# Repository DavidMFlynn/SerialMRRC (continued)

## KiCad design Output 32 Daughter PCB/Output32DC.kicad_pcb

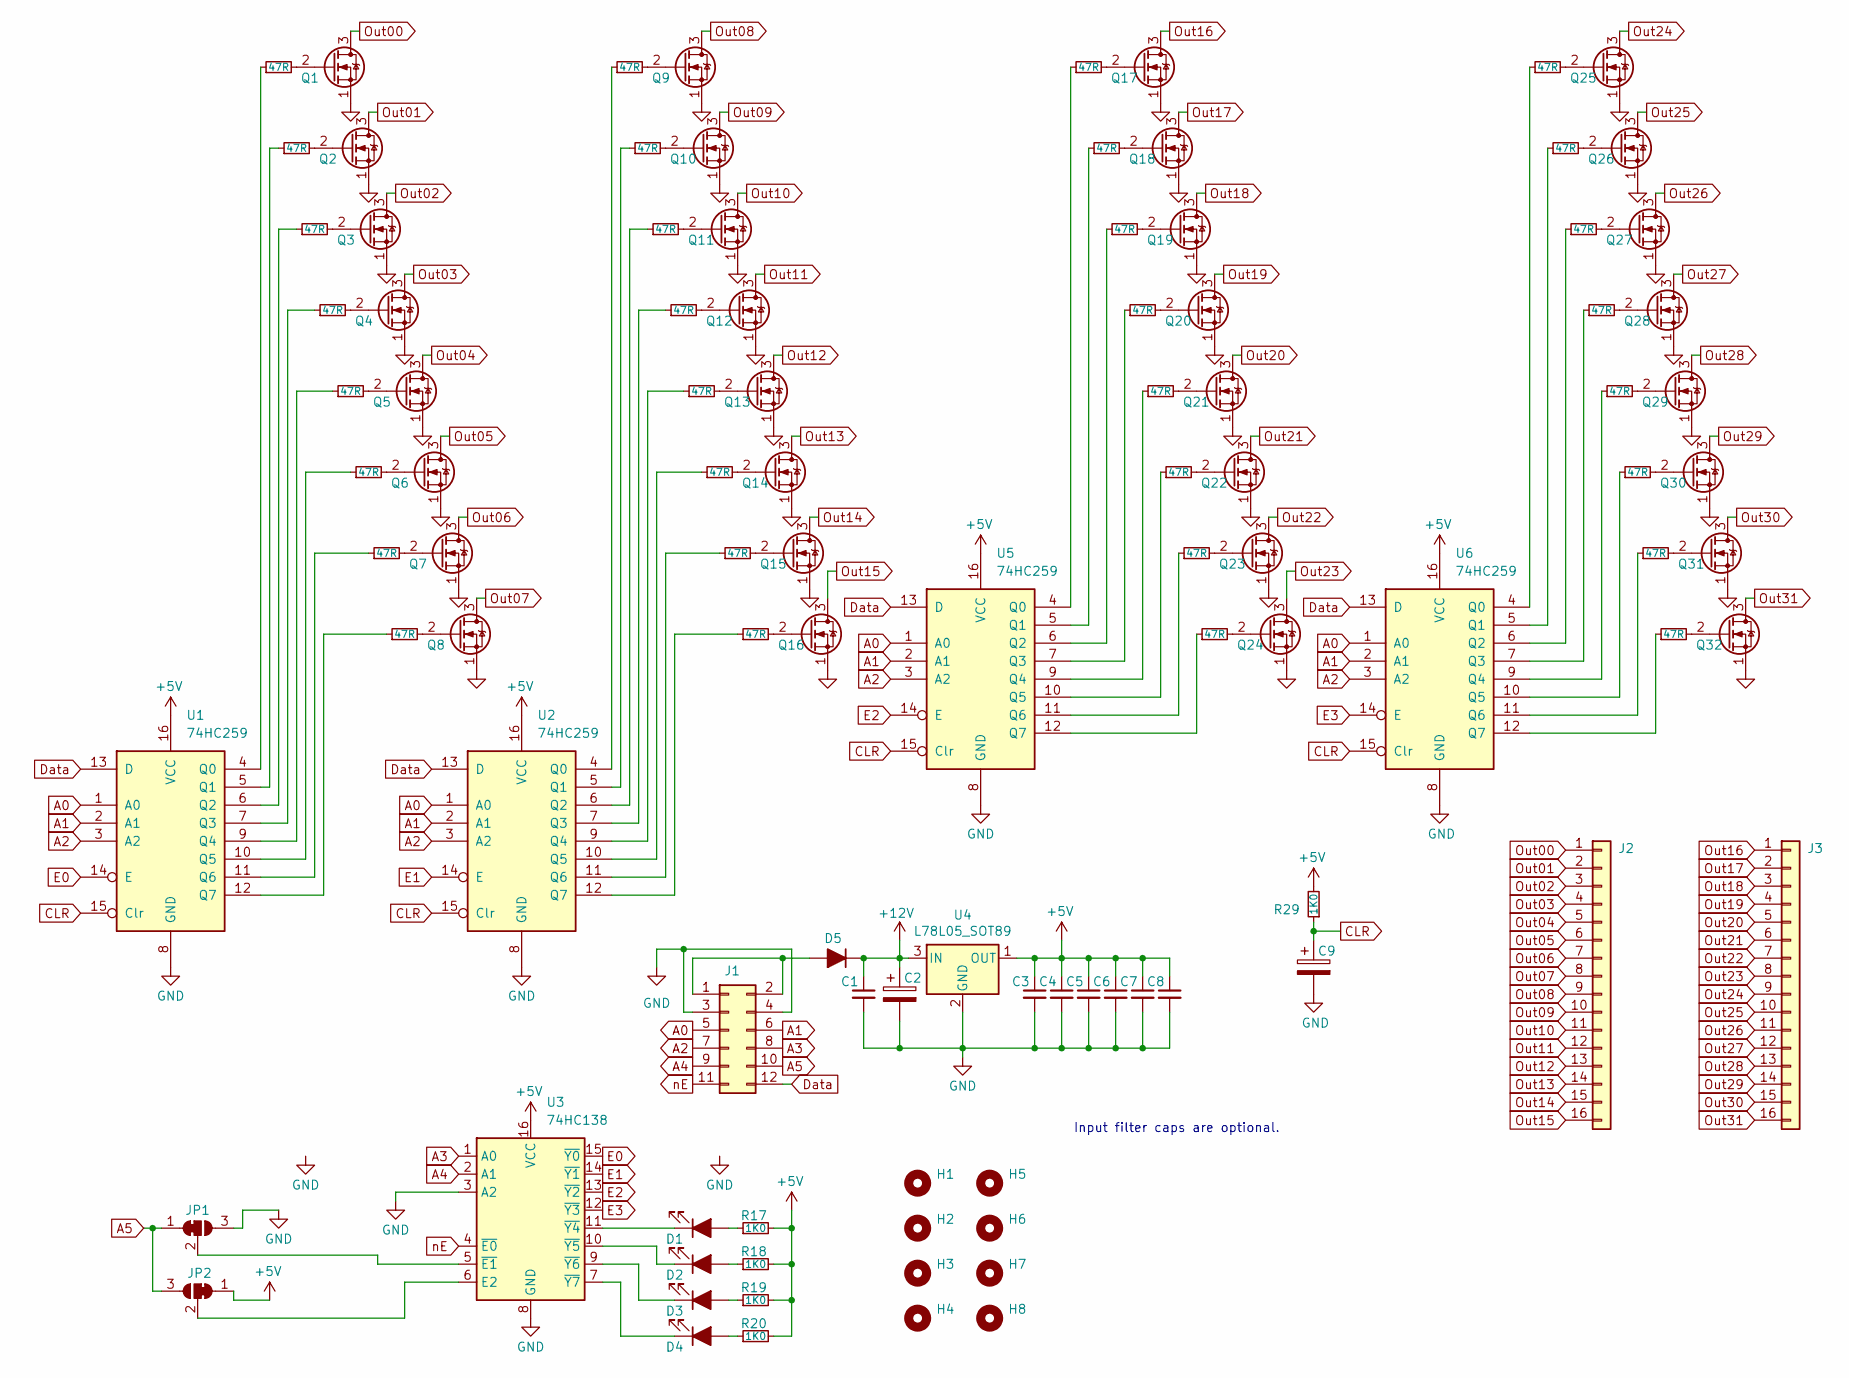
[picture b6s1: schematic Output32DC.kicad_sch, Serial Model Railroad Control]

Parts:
C1, C3, C4, C5, C6, C7, C8: 0.1uF; C_0805_2012Metric_Pad1.18x1.45mm_HandSolder
C2, C9: 10uF; CP_Radial_D5.0mm_P2.00mm
D1, D2, D3, D4: 1206 LED; LED_1206_3216Metric_Pad1.42x1.75mm_HandSolder
D5: SMA; D_SMA_Handsoldering
H1, H2, H3, H4: MountingHole; MountingHole_4.3mm_M4
H5, H6, H7, H8: MountingHole; MountingHole_3.2mm_M3
J1: Conn_02x06_Odd_Even; PinHeader_2x06_P2.54mm_Vertical
J2, J3: Conn_01x16; TerminalBlock_Phoenix_PT-1,5-16-3.5-H_1x16_P3.50mm_Horizont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
JP1, JP2: SolderJumper_3_Bridged12; SolderJumper-3_P1.3mm_Bridged12_RoundedPad1.0x1.5mm
Q1, Q2, Q3, Q4, Q5, Q6, Q7, Q8, Q9, Q10, Q11, Q12, Q13, Q14, Q15, Q16, Q17, Q18, Q19, Q20, Q21, Q22, Q23, Q24, Q25, Q26, Q27, Q28, Q29, Q30, Q31, Q32: 2N7000; TO-92_Inline
R1, R2, R3, R4, R5, R6, R7, R8, R9, R10, R11, R12, R13, R14, R15, R16, R21, R22, R23, R24, R25, R26, R27, R28, R30, R31, R32, R33, R34, R35, R36, R37: 47R; R_0805_2012Metric_Pad1.20x1.40mm_HandSolder
R17, R18, R19, R20, R29: 1K0; R_0805_2012Metric_Pad1.20x1.40mm_HandSolder
U1, U2, U5, U6: 74HC259; SOIC-16_3.9x9.9mm_P1.27mm
U3: 74HC138; SOIC-16_3.9x9.9mm_P1.27mm
U4: L78L05_SOT89; SOT-89-3

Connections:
+5V: C3.1, C4.1, C5.1, C6.1, C7.1, C8.1, JP2.1 (A), R17.2, R18.2, R19.2, R20.2, R29.2, U1.16 (VCC), U2.16 (VCC), U3.16 (VCC), U4.1 (OUT), U5.16 (VCC), U6.16 (VCC)
+12V: C1.1, C2.1, D5.1 (K), U4.3 (IN)
A0: J1.5, U1.1 (A0), U2.1 (A0), U5.1 (A0), U6.1 (A0)
A1: J1.6, U1.2 (A1), U2.2 (A1), U5.2 (A1), U6.2 (A1)
A2: J1.7, U1.3 (A2), U2.3 (A2), U5.3 (A2), U6.3 (A2)
A3: J1.8, U3.1 (A0)
A4: J1.9, U3.2 (A1)
A5: J1.10, JP1.1 (A), JP2.3 (B)
CLR: C9.1, R29.1, U1.15 (Clr), U2.15 (Clr), U5.15 (Clr), U6.15 (Clr)
Data: J1.12, U1.13 (D), U2.13 (D), U5.13 (D), U6.13 (D)
E0: U1.14 (E), U3.15 (~Y0)
E1: U2.14 (E), U3.14 (~Y1)
E2: U3.13 (~Y2), U5.14 (E)
E3: U3.12 (~Y3), U6.14 (E)
GND: C1.2, C2.2, C3.2, C4.2, C5.2, C6.2, C7.2, C8.2, C9.2, J1.3, J1.4, JP1.3 (B), Q1.1 (S), Q2.1 (S), Q3.1 (S), Q4.1 (S), Q5.1 (S), Q6.1 (S), Q7.1 (S), Q8.1 (S), Q9.1 (S), Q10.1 (S), Q11.1 (S), Q12.1 (S), Q13.1 (S), Q14.1 (S), Q15.1 (S), Q16.1 (S), Q17.1 (S), Q18.1 (S), Q19.1 (S), Q20.1 (S), Q21.1 (S), Q22.1 (S), Q23.1 (S), Q24.1 (S), Q25.1 (S), Q26.1 (S), Q27.1 (S), Q28.1 (S), Q29.1 (S), Q30.1 (S), Q31.1 (S), Q32.1 (S), U1.8 (GND), U2.8 (GND), U3.3 (A2), U3.8 (GND), U4.2 (GND), U5.8 (GND), U6.8 (GND)
unnamed: D1.2 (A), R17.1
unnamed: D1.1 (K), U3.11 (~Y4)
unnamed: D2.2 (A), R18.1
unnamed: D2.1 (K), U3.10 (~Y5)
unnamed: D3.2 (A), R19.1
unnamed: D3.1 (K), U3.9 (~Y6)
unnamed: D4.2 (A), R20.1
unnamed: D4.1 (K), U3.7 (~Y7)
unnamed: D5.2 (A), J1.1, J1.2
unnamed: JP1.2 (C), U3.5 (~E1)
unnamed: JP2.2 (C), U3.6 (E2)
unnamed: Q1.2 (G), R1.2
unnamed: Q2.2 (G), R2.2
unnamed: Q3.2 (G), R3.2
unnamed: Q4.2 (G), R4.2
unnamed: Q5.2 (G), R5.2
unnamed: Q6.2 (G), R6.2
unnamed: Q7.2 (G), R7.2
unnamed: Q8.2 (G), R8.2
unnamed: Q9.2 (G), R9.2
unnamed: Q10.2 (G), R10.2
unnamed: Q11.2 (G), R11.2
unnamed: Q12.2 (G), R12.2
unnamed: Q13.2 (G), R13.2
unnamed: Q14.2 (G), R14.2
unnamed: Q15.2 (G), R15.2
unnamed: Q16.2 (G), R16.2
unnamed: Q17.2 (G), R21.2
unnamed: Q18.2 (G), R22.2
unnamed: Q19.2 (G), R23.2
unnamed: Q20.2 (G), R24.2
unnamed: Q21.2 (G), R25.2
unnamed: Q22.2 (G), R26.2
unnamed: Q23.2 (G), R27.2
unnamed: Q24.2 (G), R28.2
unnamed: Q25.2 (G), R30.2
unnamed: Q26.2 (G), R31.2
unnamed: Q27.2 (G), R32.2
unnamed: Q28.2 (G), R33.2
unnamed: Q29.2 (G), R34.2
unnamed: Q30.2 (G), R35.2
unnamed: Q31.2 (G), R36.2
unnamed: Q32.2 (G), R37.2
unnamed: R1.1, U1.4 (Q0)
unnamed: R2.1, U1.5 (Q1)
unnamed: R3.1, U1.6 (Q2)
unnamed: R4.1, U1.7 (Q3)
unnamed: R5.1, U1.9 (Q4)
unnamed: R6.1, U1.10 (Q5)
unnamed: R7.1, U1.11 (Q6)
unnamed: R8.1, U1.12 (Q7)
unnamed: R9.1, U2.4 (Q0)
unnamed: R10.1, U2.5 (Q1)
unnamed: R11.1, U2.6 (Q2)
unnamed: R12.1, U2.7 (Q3)
unnamed: R13.1, U2.9 (Q4)
unnamed: R14.1, U2.10 (Q5)
unnamed: R15.1, U2.11 (Q6)
unnamed: R16.1, U2.12 (Q7)
unnamed: R21.1, U5.4 (Q0)
unnamed: R22.1, U5.5 (Q1)
unnamed: R23.1, U5.6 (Q2)
unnamed: R24.1, U5.7 (Q3)
unnamed: R25.1, U5.9 (Q4)
unnamed: R26.1, U5.10 (Q5)
unnamed: R27.1, U5.11 (Q6)
unnamed: R28.1, U5.12 (Q7)
unnamed: R30.1, U6.4 (Q0)
unnamed: R31.1, U6.5 (Q1)
unnamed: R32.1, U6.6 (Q2)
unnamed: R33.1, U6.7 (Q3)
unnamed: R34.1, U6.9 (Q4)
unnamed: R35.1, U6.10 (Q5)
unnamed: R36.1, U6.11 (Q6)
unnamed: R37.1, U6.12 (Q7)
Out00: J2.1, Q1.3 (D)
Out01: J2.2, Q2.3 (D)
Out02: J2.3, Q3.3 (D)
Out03: J2.4, Q4.3 (D)
Out04: J2.5, Q5.3 (D)
Out05: J2.6, Q6.3 (D)
Out06: J2.7, Q7.3 (D)
Out07: J2.8, Q8.3 (D)
Out08: J2.9, Q9.3 (D)
Out09: J2.10, Q10.3 (D)
Out10: J2.11, Q11.3 (D)
Out11: J2.12, Q12.3 (D)
Out12: J2.13, Q13.3 (D)
Out13: J2.14, Q14.3 (D)
Out14: J2.15, Q15.3 (D)
Out15: J2.16, Q16.3 (D)
Out16: J3.1, Q17.3 (D)
Out17: J3.2, Q18.3 (D)
Out18: J3.3, Q19.3 (D)
Out19: J3.4, Q20.3 (D)
Out20: J3.5, Q21.3 (D)
Out21: J3.6, Q22.3 (D)
Out22: J3.7, Q23.3 (D)
Out23: J3.8, Q24.3 (D)
Out24: J3.9, Q25.3 (D)
Out25: J3.10, Q26.3 (D)
Out26: J3.11, Q27.3 (D)
Out27: J3.12, Q28.3 (D)
Out28: J3.13, Q29.3 (D)
Out29: J3.14, Q30.3 (D)
Out30: J3.15, Q31.3 (D)
Out31: J3.16, Q32.3 (D)
nE: J1.11, U3.4 (~E0)

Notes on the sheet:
Input filter caps are optional.

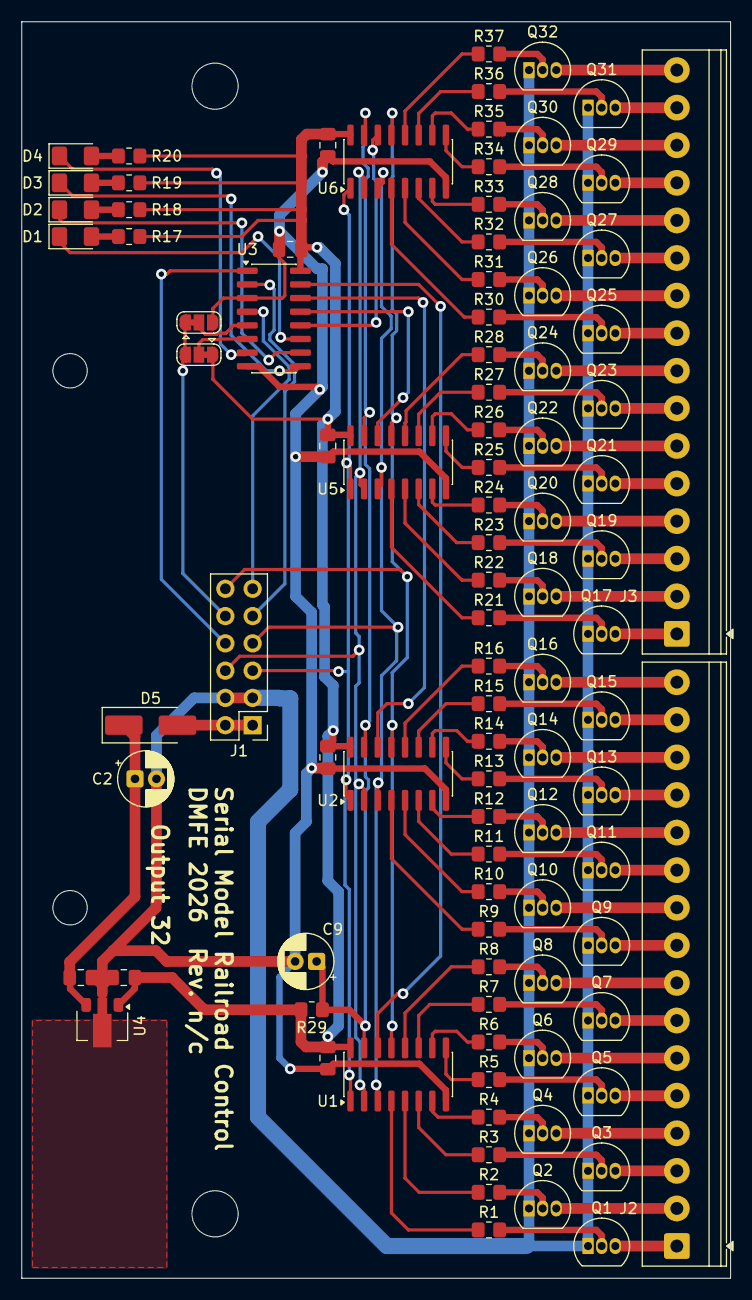
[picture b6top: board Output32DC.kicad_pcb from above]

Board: 2 copper layers, 66.0 x 117.0 mm, 98 parts (0 on the bottom side), 123 nets.

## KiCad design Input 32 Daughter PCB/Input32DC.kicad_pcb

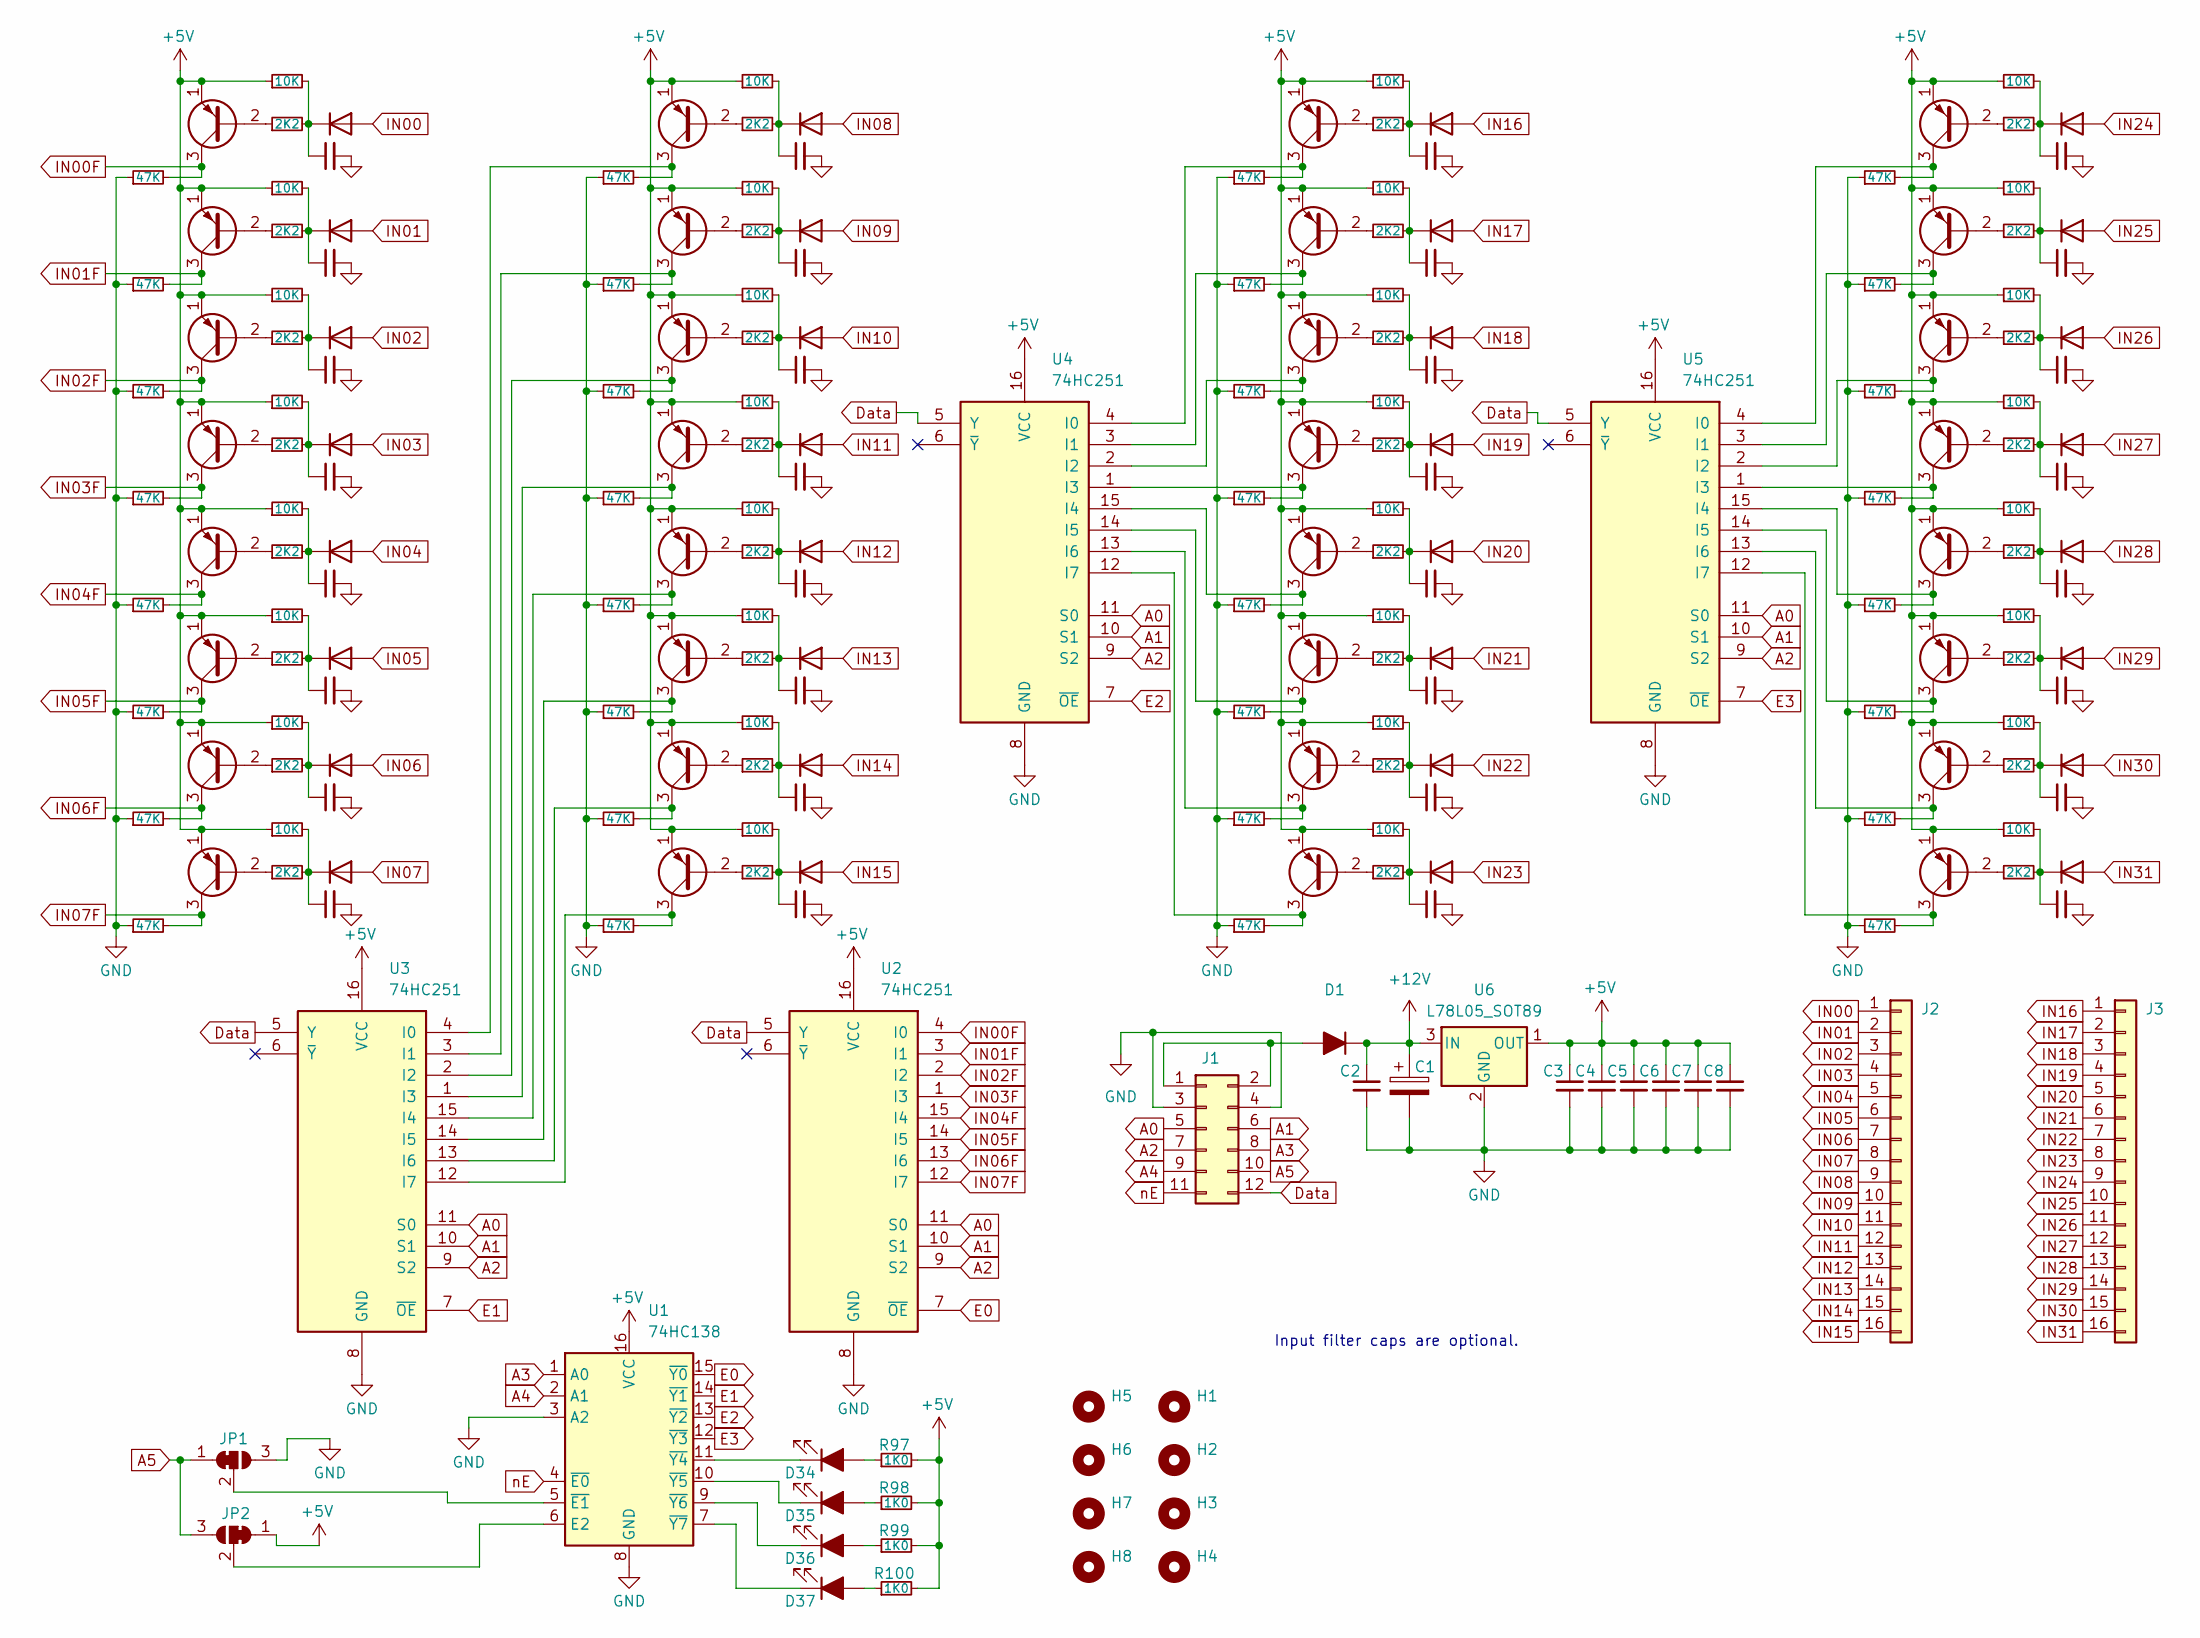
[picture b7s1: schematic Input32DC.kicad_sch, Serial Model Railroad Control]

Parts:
C1: 10uF; CP_Radial_D5.0mm_P2.00mm
C2, C3, C4, C5, C6, C7, C8, C9, C10, C11, C12, C13, C14, C15, C16, C17, C18, C19, C20, C21, C22, C23, C24, C25, C26, C27, C28, C29, C30, C31, C32, C33, C34, C35, C36, C37, C38, C39, C40: 0.1uF; C_0805_2012Metric_Pad1.18x1.45mm_HandSolder
D1: SMA; D_SMA_Handsoldering
D2, D3, D4, D5, D6, D7, D8, D9, D10, D11, D12, D13, D14, D15, D16, D17, D18, D19, D20, D21, D22, D23, D24, D25, D26, D27, D28, D29, D30, D31, D32, D33: 1N4148W; D_SOD-123
D34, D35, D36, D37: 1206 LED; LED_1206_3216Metric_Pad1.42x1.75mm_HandSolder
H1, H2, H3, H4: MountingHole; MountingHole_3.2mm_M3
H5, H6, H7, H8: MountingHole; MountingHole_4.3mm_M4
J1: Conn_02x06_Odd_Even; PinHeader_2x06_P2.54mm_Vertical
J2, J3: Conn_01x16; TerminalBlock_Phoenix_PT-1,5-16-3.5-H_1x16_P3.50mm_Horizont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
JP1, JP2: SolderJumper_3_Bridged12; SolderJumper-3_P1.3mm_Bridged12_RoundedPad1.0x1.5mm
Q2, Q3, Q4, Q5, Q6, Q7, Q8, Q9, Q10, Q11, Q12, Q13, Q14, Q15, Q16, Q17, Q18, Q19, Q20, Q21, Q22, Q23, Q24, Q25, Q26, Q27, Q28, Q29, Q30, Q31, Q32, Q33: 2N3906; TO-92_Inline
R1, R6, R9, R12, R15, R18, R21, R24, R34, R36, R38, R40, R42, R44, R46, R48, R58, R60, R62, R64, R66, R68, R70, R72, R82, R84, R86, R88, R90, R92, R94, R96: 2K2; R_0805_2012Metric_Pad1.20x1.40mm_HandSolder
R2, R5, R8, R11, R14, R17, R20, R23, R33, R35, R37, R39, R41, R43, R45, R47, R57, R59, R61, R63, R65, R67, R69, R71, R81, R83, R85, R87, R89, R91, R93, R95: 10K; R_0805_2012Metric_Pad1.20x1.40mm_HandSolder
R3, R4, R7, R10, R13, R16, R19, R22, R25, R26, R27, R28, R29, R30, R31, R32, R49, R50, R51, R52, R53, R54, R55, R56, R73, R74, R75, R76, R77, R78, R79, R80: 47K; R_0805_2012Metric_Pad1.20x1.40mm_HandSolder
R97, R98, R99, R100: 1K0; R_0805_2012Metric_Pad1.20x1.40mm_HandSolder
U1: 74HC138; SOIC-16_3.9x9.9mm_P1.27mm
U2, U3, U4, U5: 74HC251; SOIC-16_3.9x9.9mm_P1.27mm
U6: L78L05_SOT89; SOT-89-3

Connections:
+5V: C3.1, C4.1, C5.1, C6.1, C7.1, C8.1, JP2.1 (A), Q2.1 (E), Q3.1 (E), Q4.1 (E), Q5.1 (E), Q6.1 (E), Q7.1 (E), Q8.1 (E), Q9.1 (E), Q10.1 (E), Q11.1 (E), Q12.1 (E), Q13.1 (E), Q14.1 (E), Q15.1 (E), Q16.1 (E), Q17.1 (E), Q18.1 (E), Q19.1 (E), Q20.1 (E), Q21.1 (E), Q22.1 (E), Q23.1 (E), Q24.1 (E), Q25.1 (E), Q26.1 (E), Q27.1 (E), Q28.1 (E), Q29.1 (E), Q30.1 (E), Q31.1 (E), Q32.1 (E), Q33.1 (E), R2.1, R5.1, R8.1, R11.1, R14.1, R17.1, R20.1, R23.1, R33.1, R35.1, R37.1, R39.1, R41.1, R43.1, R45.1, R47.1, R57.1, R59.1, R61.1, R63.1, R65.1, R67.1, R69.1, R71.1, R81.1, R83.1, R85.1, R87.1, R89.1, R91.1, R93.1, R95.1, R97.2, R98.2, R99.2, R100.2, U1.16 (VCC), U2.16 (VCC), U3.16 (VCC), U4.16 (VCC), U5.16 (VCC), U6.1 (OUT)
+12V: C1.1, C2.1, D1.1 (K), U6.3 (IN)
A0: J1.5, U2.11 (S0), U3.11 (S0), U4.11 (S0), U5.11 (S0)
A1: J1.6, U2.10 (S1), U3.10 (S1), U4.10 (S1), U5.10 (S1)
A2: J1.7, U2.9 (S2), U3.9 (S2), U4.9 (S2), U5.9 (S2)
A3: J1.8, U1.1 (A0)
A4: J1.9, U1.2 (A1)
A5: J1.10, JP1.1 (A), JP2.3 (B)
Data: J1.12, U2.5 (Y), U3.5 (Y), U4.5 (Y), U5.5 (Y)
E0: U1.15 (~Y0), U2.7 (~OE)
E1: U1.14 (~Y1), U3.7 (~OE)
E2: U1.13 (~Y2), U4.7 (~OE)
E3: U1.12 (~Y3), U5.7 (~OE)
GND: C1.2, C2.2, C3.2, C4.2, C5.2, C6.2, C7.2, C8.2, C9.2, C10.2, C11.2, C12.2, C13.2, C14.2, C15.2, C16.2, C17.2, C18.2, C19.2, C20.2, C21.2, C22.2, C23.2, C24.2, C25.2, C26.2, C27.2, C28.2, C29.2, C30.2, C31.2, C32.2, C33.2, C34.2, C35.2, C36.2, C37.2, C38.2, C39.2, C40.2, J1.3, J1.4, JP1.3 (B), R3.1, R4.1, R7.1, R10.1, R13.1, R16.1, R19.1, R22.1, R25.1, R26.1, R27.1, R28.1, R29.1, R30.1, R31.1, R32.1, R49.1, R50.1, R51.1, R52.1, R53.1, R54.1, R55.1, R56.1, R73.1, R74.1, R75.1, R76.1, R77.1, R78.1, R79.1, R80.1, U1.3 (A2), U1.8 (GND), U2.8 (GND), U3.8 (GND), U4.8 (GND), U5.8 (GND), U6.2 (GND)
IN00: D26.2 (A), J2.1
IN00F: Q26.3 (C), R73.2, U2.4 (I0)
IN01: D27.2 (A), J2.2
IN01F: Q27.3 (C), R74.2, U2.3 (I1)
IN02: D28.2 (A), J2.3
IN02F: Q28.3 (C), R75.2, U2.2 (I2)
IN03: D29.2 (A), J2.4
IN03F: Q29.3 (C), R76.2, U2.1 (I3)
IN04: D30.2 (A), J2.5
IN04F: Q30.3 (C), R77.2, U2.15 (I4)
IN05: D31.2 (A), J2.6
IN05F: Q31.3 (C), R78.2, U2.14 (I5)
IN06: D32.2 (A), J2.7
IN06F: Q32.3 (C), R79.2, U2.13 (I6)
IN07: D33.2 (A), J2.8
IN07F: Q33.3 (C), R80.2, U2.12 (I7)
IN08: D18.2 (A), J2.9
IN09: D19.2 (A), J2.10
IN10: D20.2 (A), J2.11
IN11: D21.2 (A), J2.12
IN12: D22.2 (A), J2.13
IN13: D23.2 (A), J2.14
IN14: D24.2 (A), J2.15
IN15: D25.2 (A), J2.16
IN16: D10.2 (A), J3.1
IN17: D11.2 (A), J3.2
IN18: D12.2 (A), J3.3
IN19: D13.2 (A), J3.4
IN20: D14.2 (A), J3.5
IN21: D15.2 (A), J3.6
IN22: D16.2 (A), J3.7
IN23: D17.2 (A), J3.8
IN24: D2.2 (A), J3.9
IN25: D3.2 (A), J3.10
IN26: D4.2 (A), J3.11
IN27: D5.2 (A), J3.12
IN28: D6.2 (A), J3.13
IN29: D7.2 (A), J3.14
IN30: D8.2 (A), J3.15
IN31: D9.2 (A), J3.16
unnamed: D1.2 (A), J1.1, J1.2
unnamed: C9.1, D2.1 (K), R1.2, R2.2
unnamed: C10.1, D3.1 (K), R5.2, R6.2
unnamed: C11.1, D4.1 (K), R8.2, R9.2
unnamed: C12.1, D5.1 (K), R11.2, R12.2
unnamed: C13.1, D6.1 (K), R14.2, R15.2
unnamed: C14.1, D7.1 (K), R17.2, R18.2
unnamed: C15.1, D8.1 (K), R20.2, R21.2
unnamed: C16.1, D9.1 (K), R23.2, R24.2
unnamed: C17.1, D10.1 (K), R33.2, R34.2
unnamed: C18.1, D11.1 (K), R35.2, R36.2
unnamed: C19.1, D12.1 (K), R37.2, R38.2
unnamed: C20.1, D13.1 (K), R39.2, R40.2
unnamed: C21.1, D14.1 (K), R41.2, R42.2
unnamed: C22.1, D15.1 (K), R43.2, R44.2
unnamed: C23.1, D16.1 (K), R45.2, R46.2
unnamed: C24.1, D17.1 (K), R47.2, R48.2
unnamed: C25.1, D18.1 (K), R57.2, R58.2
unnamed: C26.1, D19.1 (K), R59.2, R60.2
unnamed: C27.1, D20.1 (K), R61.2, R62.2
unnamed: C28.1, D21.1 (K), R63.2, R64.2
unnamed: C29.1, D22.1 (K), R65.2, R66.2
unnamed: C30.1, D23.1 (K), R67.2, R68.2
unnamed: C31.1, D24.1 (K), R69.2, R70.2
unnamed: C32.1, D25.1 (K), R71.2, R72.2
unnamed: C33.1, D26.1 (K), R81.2, R82.2
unnamed: C34.1, D27.1 (K), R83.2, R84.2
unnamed: C35.1, D28.1 (K), R85.2, R86.2
unnamed: C36.1, D29.1 (K), R87.2, R88.2
unnamed: C37.1, D30.1 (K), R89.2, R90.2
unnamed: C38.1, D31.1 (K), R91.2, R92.2
unnamed: C39.1, D32.1 (K), R93.2, R94.2
unnamed: C40.1, D33.1 (K), R95.2, R96.2
unnamed: D34.2 (A), R97.1
unnamed: D34.1 (K), U1.11 (~Y4)
unnamed: D35.2 (A), R98.1
unnamed: D35.1 (K), U1.10 (~Y5)
unnamed: D36.2 (A), R99.1
unnamed: D36.1 (K), U1.9 (~Y6)
unnamed: D37.2 (A), R100.1
unnamed: D37.1 (K), U1.7 (~Y7)
unnamed: JP1.2 (C), U1.5 (~E1)
unnamed: JP2.2 (C), U1.6 (E2)
unnamed: Q2.2 (B), R1.1
unnamed: Q2.3 (C), R3.2, U5.4 (I0)
unnamed: Q3.2 (B), R6.1
unnamed: Q3.3 (C), R4.2, U5.3 (I1)
unnamed: Q4.2 (B), R9.1
unnamed: Q4.3 (C), R7.2, U5.2 (I2)
unnamed: Q5.2 (B), R12.1
unnamed: Q5.3 (C), R10.2, U5.1 (I3)
unnamed: Q6.2 (B), R15.1
unnamed: Q6.3 (C), R13.2, U5.15 (I4)
unnamed: Q7.2 (B), R18.1
unnamed: Q7.3 (C), R16.2, U5.14 (I5)
unnamed: Q8.2 (B), R21.1
unnamed: Q8.3 (C), R19.2, U5.13 (I6)
unnamed: Q9.2 (B), R24.1
unnamed: Q9.3 (C), R22.2, U5.12 (I7)
unnamed: Q10.2 (B), R34.1
unnamed: Q10.3 (C), R25.2, U4.4 (I0)
unnamed: Q11.2 (B), R36.1
unnamed: Q11.3 (C), R26.2, U4.3 (I1)
unnamed: Q12.2 (B), R38.1
unnamed: Q12.3 (C), R27.2, U4.2 (I2)
unnamed: Q13.2 (B), R40.1
unnamed: Q13.3 (C), R28.2, U4.1 (I3)
unnamed: Q14.2 (B), R42.1
unnamed: Q14.3 (C), R29.2, U4.15 (I4)
unnamed: Q15.2 (B), R44.1
unnamed: Q15.3 (C), R30.2, U4.14 (I5)
unnamed: Q16.2 (B), R46.1
unnamed: Q16.3 (C), R31.2, U4.13 (I6)
unnamed: Q17.2 (B), R48.1
unnamed: Q17.3 (C), R32.2, U4.12 (I7)
unnamed: Q18.2 (B), R58.1
unnamed: Q18.3 (C), R49.2, U3.4 (I0)
unnamed: Q19.2 (B), R60.1
unnamed: Q19.3 (C), R50.2, U3.3 (I1)
unnamed: Q20.2 (B), R62.1
unnamed: Q20.3 (C), R51.2, U3.2 (I2)
unnamed: Q21.2 (B), R64.1
unnamed: Q21.3 (C), R52.2, U3.1 (I3)
unnamed: Q22.2 (B), R66.1
unnamed: Q22.3 (C), R53.2, U3.15 (I4)
unnamed: Q23.2 (B), R68.1
unnamed: Q23.3 (C), R54.2, U3.14 (I5)
unnamed: Q24.2 (B), R70.1
unnamed: Q24.3 (C), R55.2, U3.13 (I6)
unnamed: Q25.2 (B), R72.1
unnamed: Q25.3 (C), R56.2, U3.12 (I7)
unnamed: Q26.2 (B), R82.1
unnamed: Q27.2 (B), R84.1
unnamed: Q28.2 (B), R86.1
unnamed: Q29.2 (B), R88.1
unnamed: Q30.2 (B), R90.1
unnamed: Q31.2 (B), R92.1
unnamed: Q32.2 (B), R94.1
unnamed: Q33.2 (B), R96.1
nE: J1.11, U1.4 (~E0)

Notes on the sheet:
Input filter caps are optional.

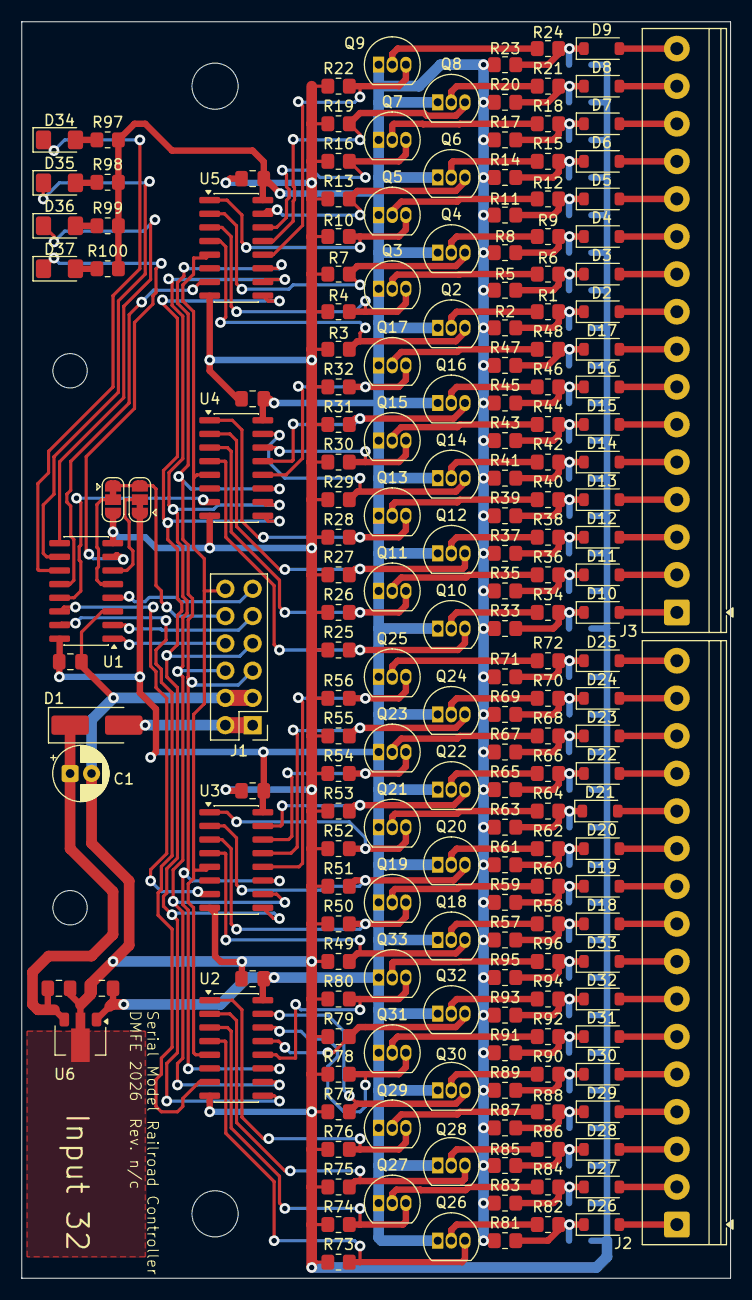
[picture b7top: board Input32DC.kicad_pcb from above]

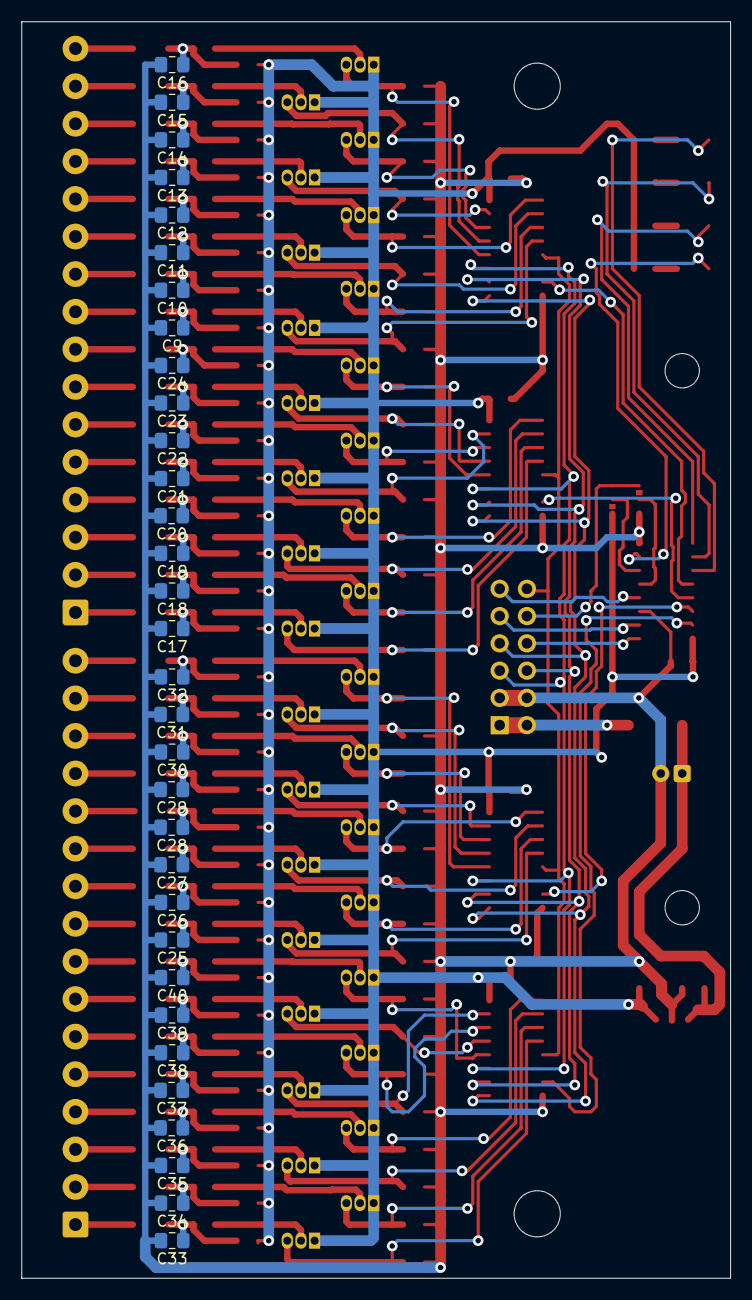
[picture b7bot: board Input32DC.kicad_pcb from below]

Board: 2 copper layers, 66.0 x 117.0 mm, 224 parts (32 on the bottom side), 154 nets.

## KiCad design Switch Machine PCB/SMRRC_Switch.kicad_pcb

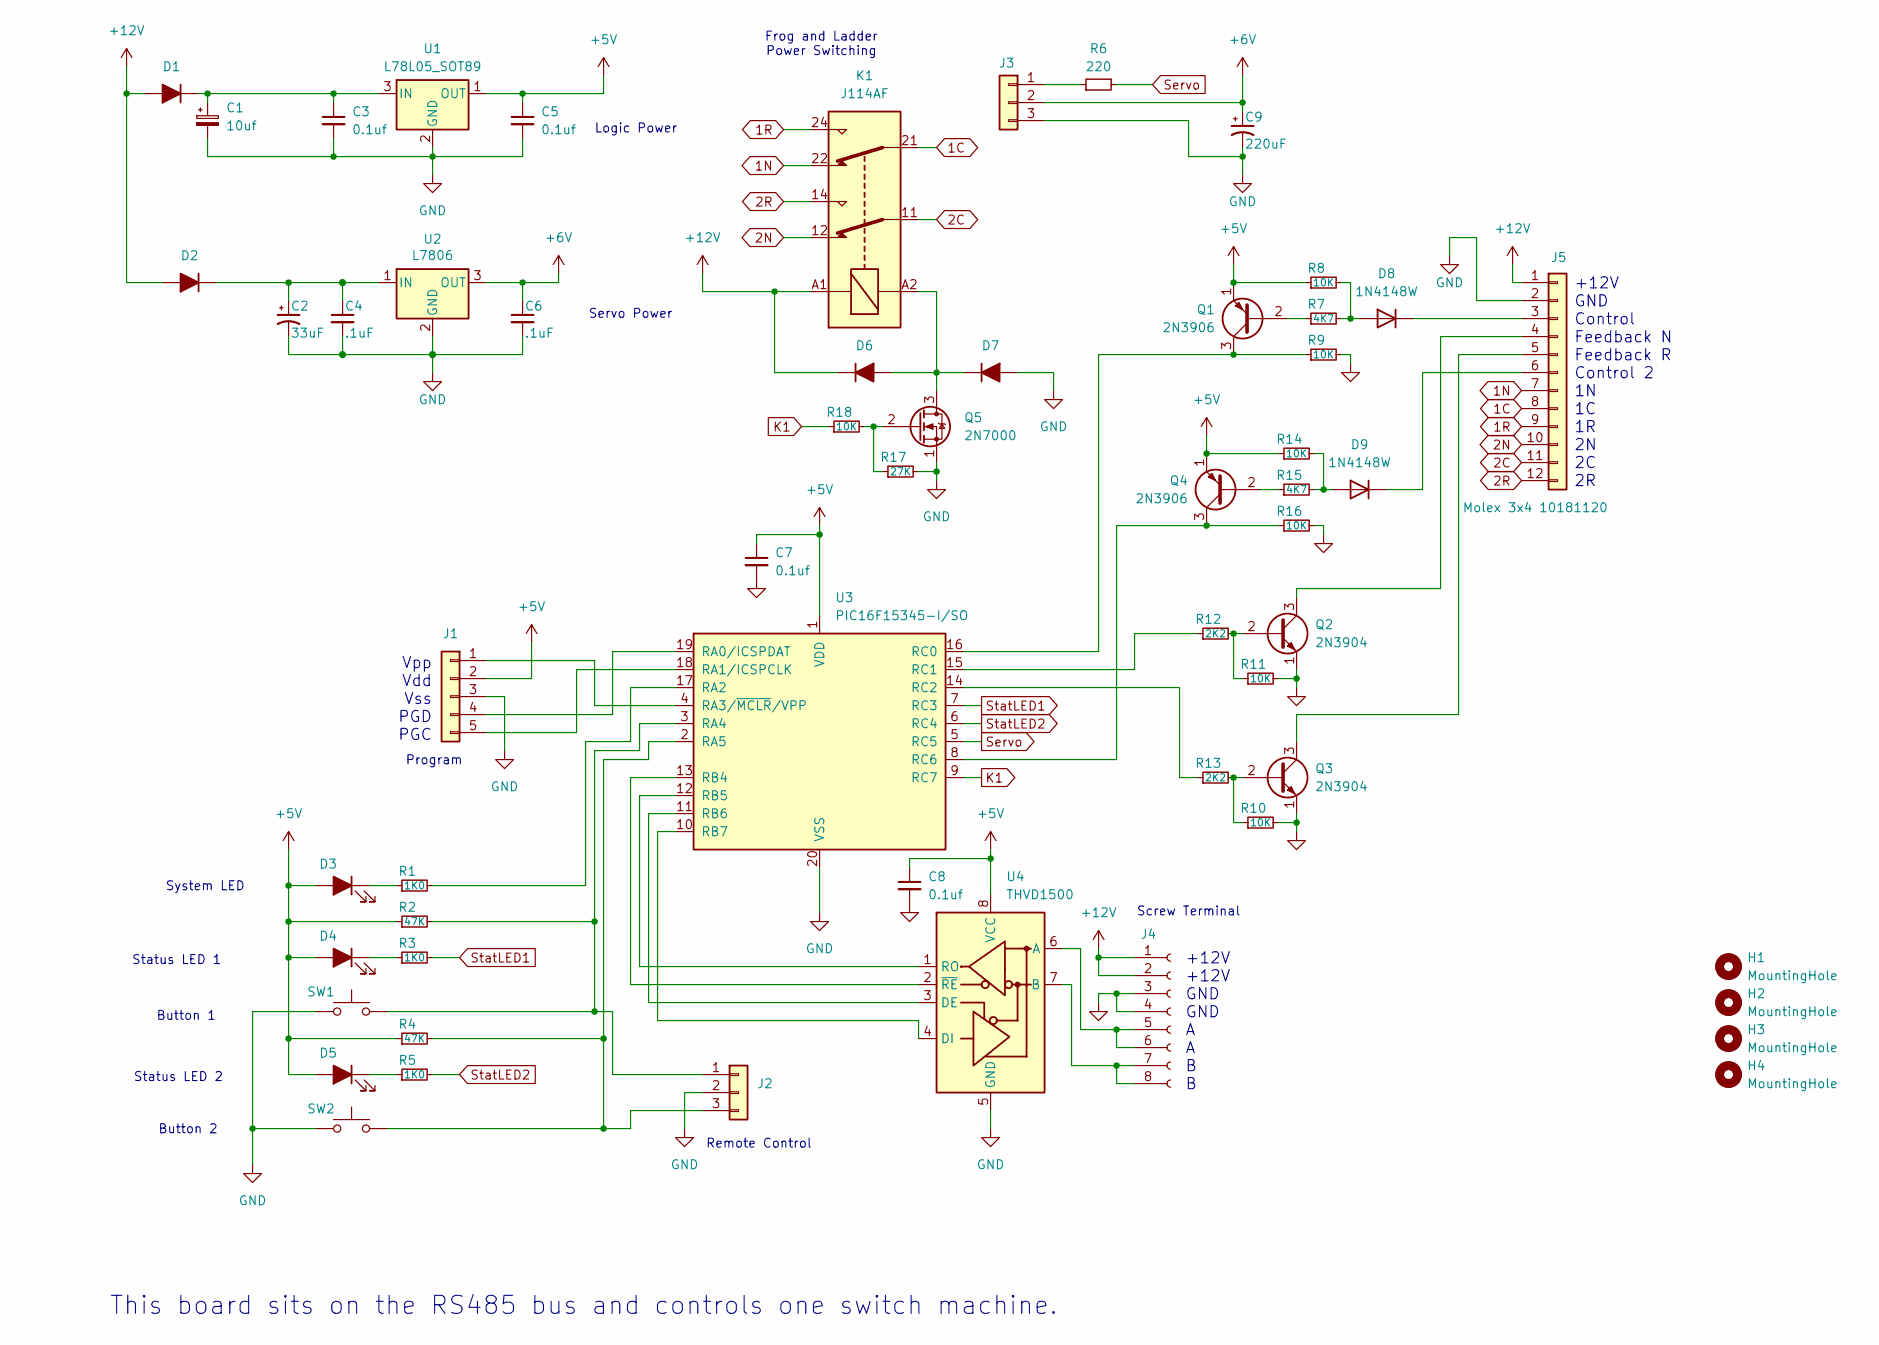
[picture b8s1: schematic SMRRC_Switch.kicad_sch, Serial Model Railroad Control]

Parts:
C1: 10uf; CP_Radial_D4.0mm_P2.00mm
C2: 33uF; CP_Radial_D5.0mm_P2.00mm
C3, C5, C7, C8: 0.1uf; C_0805_2012Metric_Pad1.18x1.45mm_HandSolder
C4, C6: .1uF; C_0805_2012Metric_Pad1.18x1.45mm_HandSolder
C9: 220uF; CP_Radial_D6.3mm_P2.50mm
D1, D2, D6, D7: SMA; D_SMA_Handsoldering
D3, D4, D5: LED_Filled; D_1206_3216Metric_Pad1.42x1.75mm_HandSolder
D8, D9: 1N4148W; D_SOD-123
H1, H2, H3, H4: MountingHole; MountingHole_3.2mm_M3
J1: Conn_01x05; PinHeader_1x05_P2.54mm_Vertical
J2: Conn_01x03; PinSocket_1x03_P2.54mm_Vertical
J3: Conn_01x03; PinHeader_1x03_P2.54mm_Vertical
J4: Conn_01x08_Socket; TerminalBlock_MaiXu_MX126-5.0-08P_1x08_P5.00mm
J5: Molex 3x4 10181120; Molex10181120
K1: J114AF; Relay_DPDT_Finder_40.52
Q1, Q4: 2N3906; TO-92_Inline
Q2, Q3: 2N3904; TO-92_Inline
Q5: 2N7000; TO-92_Inline
R1, R3, R5: 1K0; R_0805_2012Metric_Pad1.20x1.40mm_HandSolder
R2, R4: 47K; R_0805_2012Metric_Pad1.20x1.40mm_HandSolder
R6: 220; R_0805_2012Metric_Pad1.20x1.40mm_HandSolder
R7, R15: 4K7; R_0805_2012Metric_Pad1.20x1.40mm_HandSolder
R8, R9, R10, R11, R14, R16, R18: 10K; R_0805_2012Metric_Pad1.20x1.40mm_HandSolder
R12, R13: 2K2; R_0805_2012Metric_Pad1.20x1.40mm_HandSolder
R17: 27K; R_0805_2012Metric_Pad1.20x1.40mm_HandSolder
SW1, SW2: SW_Push; SW_SPST_PTS645
U1: L78L05_SOT89; SOT-89-3
U2: L7806; TO-263-2
U3: PIC16F15345-I/SO; SOIC-20W_7.5x12.8mm_P1.27mm
U4: THVD1500; SOIC-8_3.9x4.9mm_P1.27mm

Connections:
1C: J5.8, K1.21
1N: J5.7, K1.22
1R: J5.9, K1.24
2C: J5.11, K1.11
2N: J5.10, K1.12
2R: J5.12, K1.14
+5V: C5.1, C7.1, C8.1, D3.2 (A), D4.2 (A), D5.2 (A), J1.2, Q1.1 (E), Q4.1 (E), R2.1, R4.1, R8.1, R14.1, U1.1 (OUT), U3.1 (VDD), U4.8 (VCC)
+6V: C6.1, C9.1, J3.2, U2.3 (OUT)
+12V: D1.2 (A), D2.2 (A), D6.1 (K), J4.1, J4.2, J5.1, K1.A1
GND: C1.2, C2.2, C3.2, C4.2, C5.2, C6.2, C7.2, C8.2, C9.2, D7.2 (A), J1.3, J2.2, J3.3, J4.3, J4.4, J5.2, Q2.1 (E), Q3.1 (E), Q5.1 (S), R9.2, R10.2, R11.2, R16.2, R17.2, SW1.1, SW2.1, U1.2 (GND), U2.2 (GND), U3.20 (VSS), U4.5 (GND)
K1: R18.1, U3.9 (RC7)
unnamed: C1.1, C3.1, D1.1 (K), U1.3 (IN)
unnamed: C2.1, C4.1, D2.1 (K), U2.1 (IN)
unnamed: D3.1 (K), R1.1
unnamed: D4.1 (K), R3.1
unnamed: D5.1 (K), R5.1
unnamed: D6.2 (A), D7.1 (K), K1.A2, Q5.3 (D)
unnamed: D8.2 (A), R7.2, R8.2
unnamed: D8.1 (K), J5.3
unnamed: D9.2 (A), R14.2, R15.2
unnamed: D9.1 (K), J5.6
unnamed: J1.1, U3.4 (RA3/~MCLR/VPP)
unnamed: J1.4, U3.19 (RA0/ICSPDAT)
unnamed: J1.5, U3.18 (RA1/ICSPCLK)
unnamed: J2.1, R2.2, SW1.2, U3.3 (RA4)
unnamed: J2.3, R4.2, SW2.2, U3.2 (RA5)
unnamed: J3.1, R6.1
unnamed: J4.5, J4.6, U4.6 (A)
unnamed: J4.7, J4.8, U4.7 (B)
unnamed: J5.4, Q2.3 (C)
unnamed: J5.5, Q3.3 (C)
unnamed: Q1.2 (B), R7.1
unnamed: Q1.3 (C), R9.1, U3.16 (RC0)
unnamed: Q2.2 (B), R11.1, R12.2
unnamed: Q3.2 (B), R10.1, R13.2
unnamed: Q4.2 (B), R15.1
unnamed: Q4.3 (C), R16.1, U3.8 (RC6)
unnamed: Q5.2 (G), R17.1, R18.2
unnamed: R1.2, U3.17 (RA2)
unnamed: U3.13 (RB4), U4.2 (~RE)
unnamed: U3.12 (RB5), U4.1 (RO)
unnamed: U3.11 (RB6), U4.3 (DE)
unnamed: U3.10 (RB7), U4.4 (DI)
unnamed: R12.1, U3.15 (RC1)
unnamed: R13.1, U3.14 (RC2)
Servo: R6.2, U3.5 (RC5)
StatLED1: R3.2, U3.7 (RC3)
StatLED2: R5.2, U3.6 (RC4)

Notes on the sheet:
Servo Power
Remote Control
Vpp Vdd Vss PGD PGC
Button 2
Screw Terminal
Program
+12V +12V GND GND A A B B
Status LED 2
Button 1
Frog and Ladder Power Switching
Status LED 1
This board sits on the RS485 bus and controls one switch machine.
Logic Power
System LED
+12V GND Control Feedback N Feedback R Control 2 1N 1C 1R 2N 2C 2R

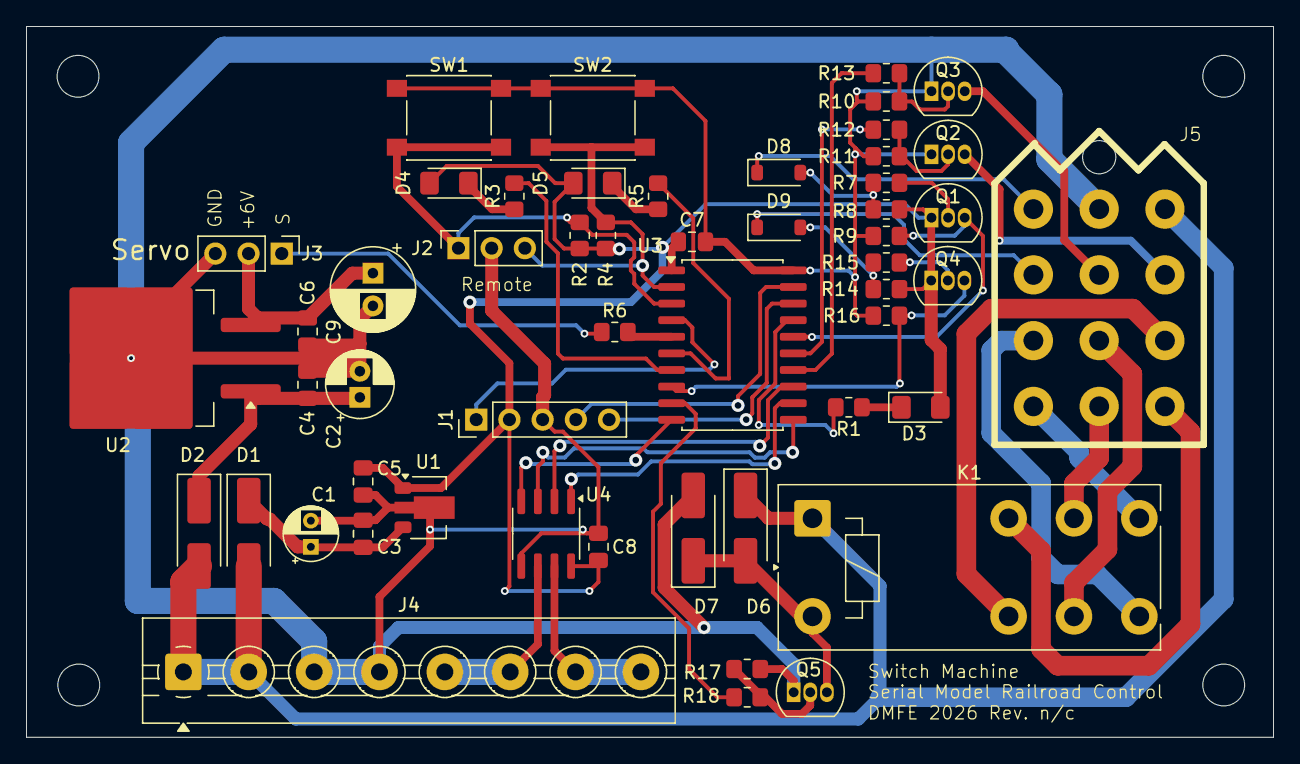
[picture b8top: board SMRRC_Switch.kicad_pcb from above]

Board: 2 copper layers, 95.4 x 54.4 mm, 57 parts (0 on the bottom side), 48 nets.
